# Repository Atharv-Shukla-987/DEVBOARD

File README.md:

# DEVBOARD
It is devboard made with the help of rp2040 . I try to make it as compact as possible  thus it is a square shaped devboard .It also have many gpio pins. It has following features

##### It has usb C port
##### It has 16MB external QSPI flash
##### It has 1 VBUS , 3v3 and Clock pins 
##### It has 29 gpio pins
##### It has tactile push button for reset

 ## COMPONENTS
#### RP2040
#### MCP1700x-3.3V LDO Regulator (TO-92)
#### W25Q128JVS — 128Mb SPI Flash (SOIC-8)
#### 12 MHz Crystal Oscillator
#### USB-C Receptacle
#### Pin HeaderS
#### Tactile Push Button
#### Capacitors
#### Resistors
 
 ## SCHEMATICS
 I have designed this devboard using kicad. Here are some images

 ### RP2040

### USB

### PINOUT

### FLASH STROAGE

### CRYSTAL OSCILLATOR

### DECOUPLING

## FOOTPRINTS

## PCB EDITOR
This is how I traced my devboad.Here its image 

## 3D VIEW

This how it will look in real life.

### Front

### Back

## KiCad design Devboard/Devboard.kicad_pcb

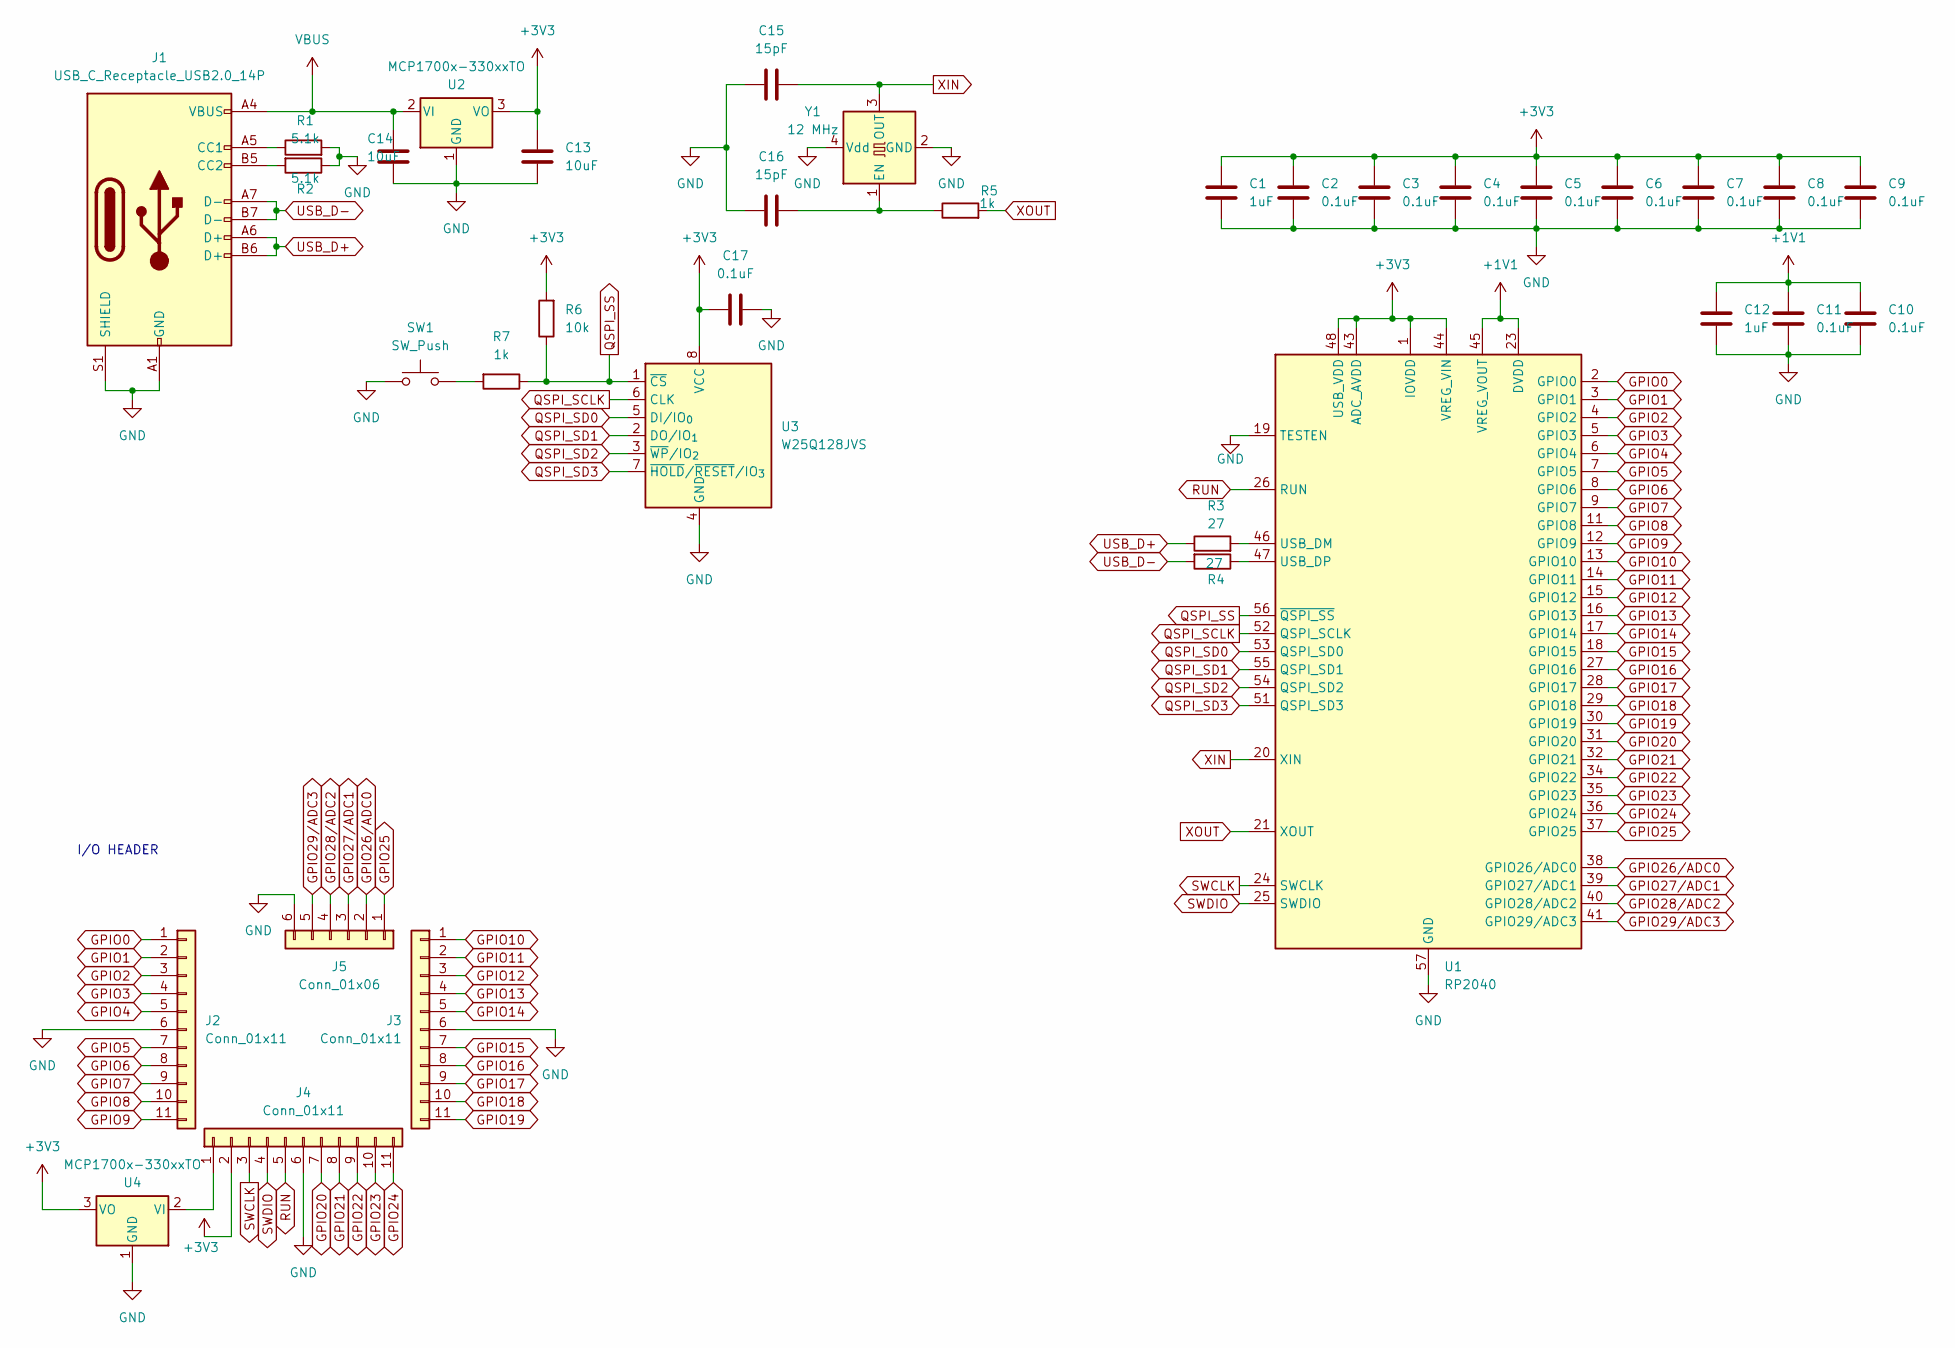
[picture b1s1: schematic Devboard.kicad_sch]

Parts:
C1, C12: 1uF; C_0402_1005Metric
C2, C3, C4, C5, C6, C7, C8, C9, C10, C11, C17: 0.1uF; C_0402_1005Metric
C13, C14: 10uF; C_0603_1608Metric
C15, C16: 15pF; C_0603_1608Metric
J1: USB_C_Receptacle_USB2.0_14P; USB_C_Receptacle_HRO_TYPE-C-31-M-12
J2, J3, J4: Conn_01x11; PinHeader_1x11_P2.54mm_Vertical
J5: Conn_01x06; PinHeader_1x06_P2.54mm_Vertical
R1, R2: 5.1k; R_0402_1005Metric
R3, R4: 27; R_0402_1005Metric
R5, R7: 1k; R_0402_1005Metric
R6: 10k; R_0402_1005Metric
SW1: SW_Push; SW_Push_SPST_NO_Alps_SKRK
U1: RP2040; QFN-56-1EP_7x7mm_P0.4mm_EP3.2x3.2mm
U2, U4: MCP1700x-330xxTO; TO-92_Inline
U3: W25Q128JVS; SOIC-8_5.3x5.3mm_P1.27mm
Y1: 12 MHz; Oscillator_SMD_Abracon_ASE-4Pin_3.2x2.5mm

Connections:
+1V1: C10.1, C11.1, C12.1, U1.23 (DVDD), U1.45 (VREG_VOUT), U1.50 (DVDD)
+3V3: C1.1, C2.1, C3.1, C4.1, C5.1, C6.1, C7.1, C8.1, C9.1, C13.1, C17.1, J4.2, R6.2, U1.1 (IOVDD), U1.10 (IOVDD), U1.22 (IOVDD), U1.33 (IOVDD), U1.42 (IOVDD), U1.43 (ADC_AVDD), U1.44 (VREG_VIN), U1.48 (USB_VDD), U1.49 (IOVDD), U2.3 (VO), U3.8 (VCC), U4.3 (VO)
GND: C1.2, C2.2, C3.2, C4.2, C5.2, C6.2, C7.2, C8.2, C9.2, C10.2, C11.2, C12.2, C13.2, C14.2, C15.1, C16.1, C17.2, J1.A1 (GND), J1.A12 (GND), J1.B1 (GND), J1.B12 (GND), J1.S1 (SHIELD), J2.6, J3.6, J4.6, J5.6, R1.2, R2.1, SW1.1, U1.19 (TESTEN), U1.57 (GND), U2.1 (GND), U3.4 (GND), U4.1 (GND), Y1.2 (GND), Y1.4 (Vdd)
GPIO0: J2.1, U1.2 (GPIO0)
GPIO1: J2.2, U1.3 (GPIO1)
GPIO2: J2.3, U1.4 (GPIO2)
GPIO3: J2.4, U1.5 (GPIO3)
GPIO4: J2.5, U1.6 (GPIO4)
GPIO5: J2.7, U1.7 (GPIO5)
GPIO6: J2.8, U1.8 (GPIO6)
GPIO7: J2.9, U1.9 (GPIO7)
GPIO8: J2.10, U1.11 (GPIO8)
GPIO9: J2.11, U1.12 (GPIO9)
GPIO10: J3.1, U1.13 (GPIO10)
GPIO11: J3.2, U1.14 (GPIO11)
GPIO12: J3.3, U1.15 (GPIO12)
GPIO13: J3.4, U1.16 (GPIO13)
GPIO14: J3.5, U1.17 (GPIO14)
GPIO15: J3.7, U1.18 (GPIO15)
GPIO16: J3.8, U1.27 (GPIO16)
GPIO17: J3.9, U1.28 (GPIO17)
GPIO18: J3.10, U1.29 (GPIO18)
GPIO19: J3.11, U1.30 (GPIO19)
GPIO20: J4.7, U1.31 (GPIO20)
GPIO21: J4.8, U1.32 (GPIO21)
GPIO22: J4.9, U1.34 (GPIO22)
GPIO23: J4.10, U1.35 (GPIO23)
GPIO24: J4.11, U1.36 (GPIO24)
GPIO25: J5.1, U1.37 (GPIO25)
GPIO26/ADC0: J5.2, U1.38 (GPIO26/ADC0)
GPIO27/ADC1: J5.3, U1.39 (GPIO27/ADC1)
GPIO28/ADC2: J5.4, U1.40 (GPIO28/ADC2)
GPIO29/ADC3: J5.5, U1.41 (GPIO29/ADC3)
unnamed: J1.A5 (CC1), R1.1
unnamed: J1.B5 (CC2), R2.2
unnamed: J4.1, U4.2 (VI)
unnamed: R7.2, SW1.2
unnamed: R3.2, U1.46 (USB_DM)
unnamed: R4.1, U1.47 (USB_DP)
unnamed: C16.2, R5.1, Y1.1 (EN)
QSPI_SCLK: U1.52 (QSPI_SCLK), U3.6 (CLK)
QSPI_SD0: U1.53 (QSPI_SD0), U3.5 (DI/IO_{0})
QSPI_SD1: U1.55 (QSPI_SD1), U3.2 (DO/IO_{1})
QSPI_SD2: U1.54 (QSPI_SD2), U3.3 (~WP/IO_{2})
QSPI_SD3: U1.51 (QSPI_SD3), U3.7 (~HOLD/~RESET/IO_{3})
QSPI_SS: R6.1, R7.1, U1.56 (~QSPI_SS), U3.1 (~CS)
RUN: J4.5, U1.26 (RUN)
SWCLK: J4.3, U1.24 (SWCLK)
SWDIO: J4.4, U1.25 (SWDIO)
USB_D+: J1.A6 (D+), J1.B6 (D+), R3.1
USB_D-: J1.A7 (D-), J1.B7 (D-), R4.2
VBUS: C14.1, J1.A4 (VBUS), J1.A9 (VBUS), J1.B4 (VBUS), J1.B9 (VBUS), U2.2 (VI)
XIN: C15.2, U1.20 (XIN), Y1.3 (OUT)
XOUT: R5.2, U1.21 (XOUT)

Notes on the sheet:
I/O HEADER

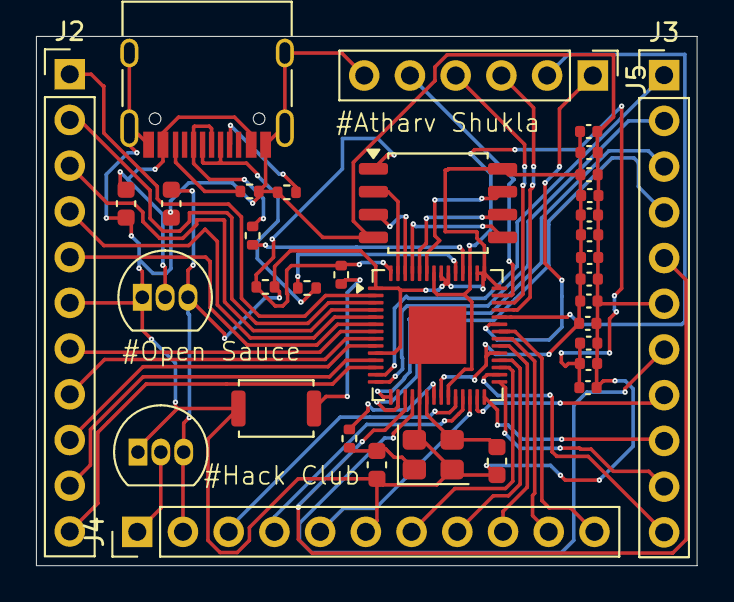
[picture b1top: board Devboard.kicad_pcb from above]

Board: 2 copper layers, 36.7 x 29.4 mm, 35 parts (0 on the bottom side), 54 nets.
